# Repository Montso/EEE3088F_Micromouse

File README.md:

# EEE3080F Micromouse Project
This repo consists of the KiCAD files the sensing and power components of the micromouse project.

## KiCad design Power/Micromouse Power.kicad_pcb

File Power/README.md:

Power board for the micromouse projecct under EEE3088F.

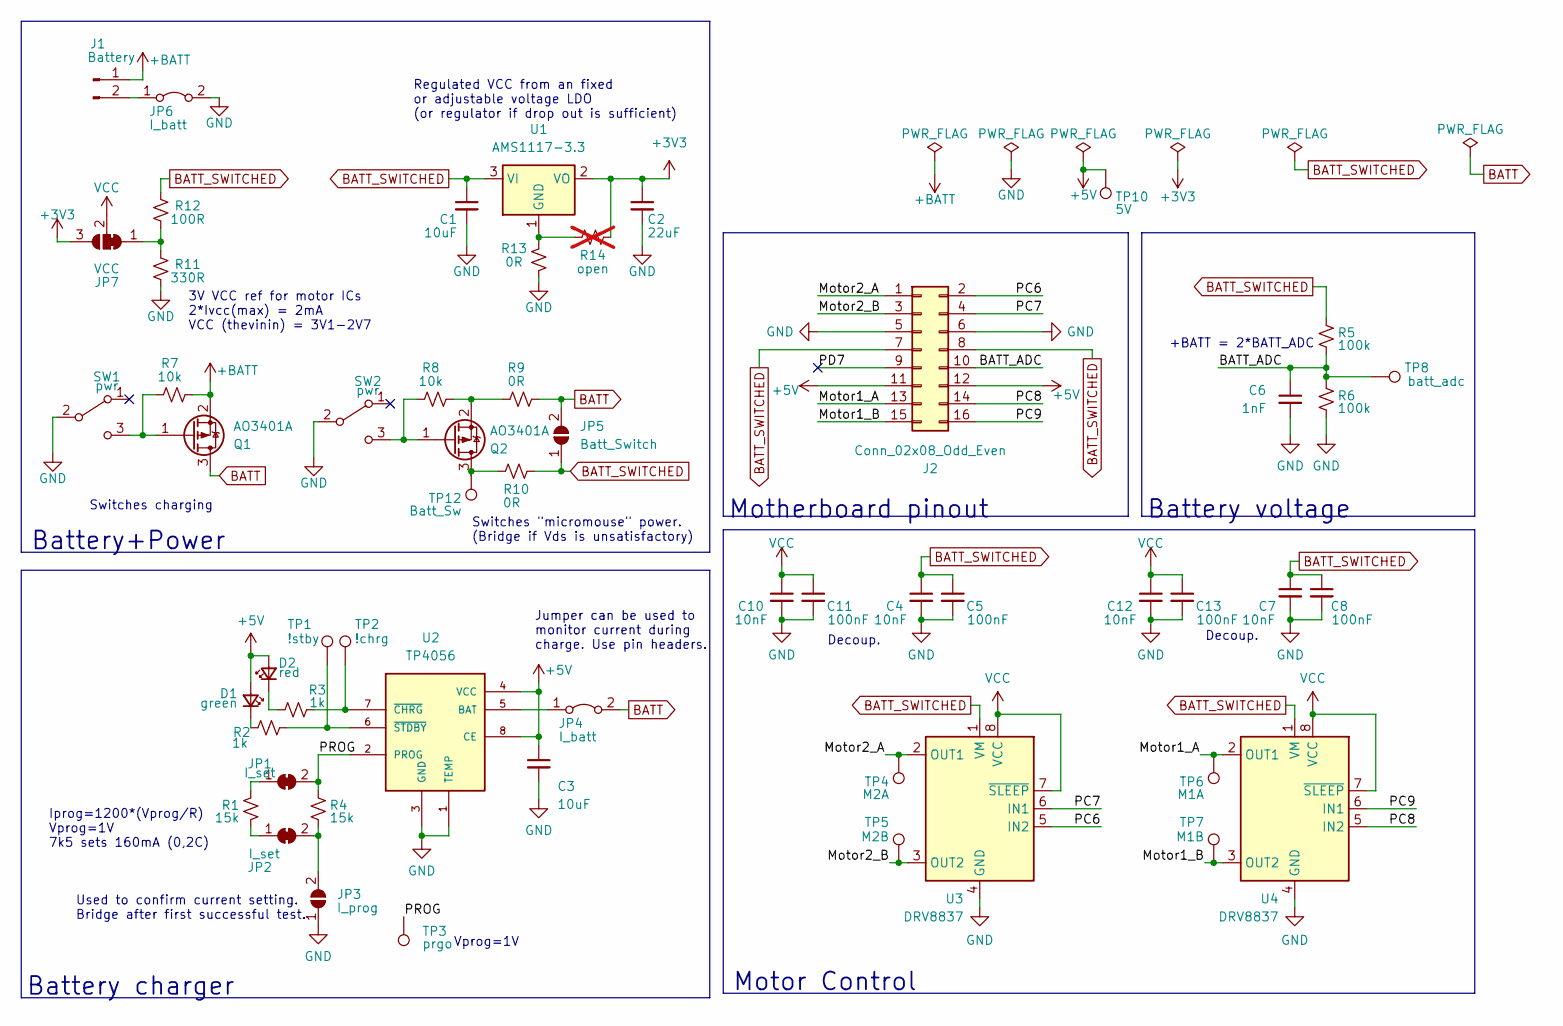
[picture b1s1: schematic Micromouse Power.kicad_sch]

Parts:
C1, C3: 10uF; C_0603_1608Metric; LCSC C19702
C2: 22uF; C_0603_1608Metric; LCSC C59461
C4, C7, C10, C12: 10nF; C_0603_1608Metric; LCSC C57112
C5, C8, C11, C13: 100nF; C_0603_1608Metric; LCSC C14663
C6: 1nF; C_0603_1608Metric; LCSC C1588
D1: green; LED_0603_1608Metric; LCSC C72038
D2: red; LED_0603_1608Metric; LCSC C2286
J1: Battery; JST_PH_S2B-PH-K_1x02_P2.00mm_Horizontal
J2: Conn_02x08_Odd_Even; PinHeader_2x08_P2.54mm_Vertical
JP1, JP2: I_set; SolderJumper-2_P1.3mm_Bridged_RoundedPad1.0x1.5mm
JP3: I_prog; SolderJumper-2_P1.3mm_Open_RoundedPad1.0x1.5mm
JP4, JP6: I_batt; PinHeader_1x02_P2.54mm_Vertical
JP5: Batt_Switch; SolderJumper-2_P1.3mm_Open_RoundedPad1.0x1.5mm
JP7: VCC; SolderJumper-3_P1.3mm_Bridged12_Pad1.0x1.5mm_NumberLabels
Q1, Q2: AO3401A; SOT-23; LCSC C15127
R1, R4: 15k; R_0805_2012Metric_Pad1.20x1.40mm_HandSolder; LCSC C17475
R2, R3: 1k; R_0603_1608Metric_Pad0.98x0.95mm_HandSolder; LCSC C21190
R5, R6: 100k; R_0603_1608Metric_Pad0.98x0.95mm_HandSolder; LCSC C25803
R7, R8: 10k; R_0603_1608Metric_Pad0.98x0.95mm_HandSolder; LCSC C25804
R9, R10, R13: 0R; R_0603_1608Metric_Pad0.98x0.95mm_HandSolder; LCSC C21189
R11: 330R; R_0603_1608Metric_Pad0.98x0.95mm_HandSolder; LCSC C23138
R12: 100R; R_0603_1608Metric_Pad0.98x0.95mm_HandSolder; LCSC C22775
R14: open; R_0603_1608Metric_Pad0.98x0.95mm_HandSolder; not fitted
SW1, SW2: pwr; SMD_SPDT; LCSC C145857
TP1: !stby; TestPoint_Pad_D1.0mm
TP2: !chrg; TestPoint_Pad_D1.0mm
TP3: prgo; TestPoint_Pad_D1.0mm
TP4: M2A; TestPoint_Pad_D1.0mm
TP5: M2B; TestPoint_Pad_D1.0mm
TP6: M1A; TestPoint_Pad_D1.0mm
TP7: M1B; TestPoint_Pad_D1.0mm
TP8: batt_adc; TestPoint_Pad_D1.0mm
TP10: 5V; TestPoint_Pad_D1.0mm
TP12: Batt_Sw; TestPoint_Pad_D1.0mm
U1: AMS1117-3.3; SOT-223-3_TabPin2; LCSC C6186
U2: TP4056; SOP127P600X175-9N; LCSC C16581
U3, U4: DRV8837; WSON-8-1EP_2x2mm_P0.5mm_EP0.9x1.6mm; LCSC C191000

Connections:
+3V3: C2.1, JP7.3 (B), R14.1, U1.2 (VO)
+5V: C3.1, D1.2 (A), D2.2 (A), J2.11, J2.12, TP10.1, U2.4 (VCC), U2.8 (CE)
+BATT: J1.1, Q1.2 (S), R7.1
/BATT_ADC: C6.1, J2.10, R5.1, R6.2, TP8.1
/Motor1_A: J2.13, TP6.1, U4.2 (OUT1)
/Motor1_B: J2.15, TP7.1, U4.3 (OUT2)
/Motor2_A: J2.1, TP4.1, U3.2 (OUT1)
/Motor2_B: J2.3, TP5.1, U3.3 (OUT2)
/PC6: J2.2, U3.5 (IN2)
/PC7: J2.4, U3.6 (IN1)
/PC8: J2.14, U4.5 (IN2)
/PC9: J2.16, U4.6 (IN1)
/PD7: J2.9
/PROG: JP1.2 (B), R4.2, TP3.1, U2.2 (PROG)
BATT: JP4.2 (B), JP5.2 (B), Q1.3 (D), R9.1
BATT_SWITCHED: C1.1, C4.1, C5.1, C7.1, C8.1, J2.7, J2.8, JP5.1 (A), R5.2, R10.2, R12.1, U1.3 (VI), U3.1 (VM), U4.1 (VM)
GND: C1.2, C2.2, C3.2, C4.2, C5.2, C6.2, C7.2, C8.2, C10.2, C11.2, C12.2, C13.2, J2.5, J2.6, JP3.1 (A), JP6.2 (B), R6.1, R11.2, R13.1, SW1.2 (B), SW2.2 (B), U2.1 (TEMP), U2.3 (GND), U3.4 (GND), U3.9 (GND), U4.4 (GND), U4.9 (GND)
unnamed: D1.1 (K), R2.1
unnamed: D2.1 (K), R3.1
unnamed: J1.2, JP6.1 (A)
unnamed: JP1.1 (A), R1.2
unnamed: JP2.1 (A), R1.1
unnamed: JP2.2 (B), JP3.2 (B), R4.1
unnamed: JP4.1 (A), U2.5 (BAT)
unnamed: JP7.1 (A), R11.1, R12.2
unnamed: Q1.1 (G), R7.2, SW1.3 (C)
unnamed: Q2.3 (D), R10.1, TP12.1
unnamed: Q2.1 (G), R8.2, SW2.3 (C)
unnamed: Q2.2 (S), R8.1, R9.2
unnamed: R13.2, R14.2, U1.1 (GND)
unnamed: R3.2, TP2.1, U2.7 (~CHRG)
unnamed: R2.2, TP1.1, U2.6 (~STDBY)
VCC: C10.1, C11.1, C12.1, C13.1, JP7.2 (C), U3.7 (~SLEEP), U3.8 (VCC), U4.7 (~SLEEP), U4.8 (VCC)

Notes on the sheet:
Battery+Power
Regulated VCC from an fixed or adjustable voltage LDO (or regulator if drop out is sufficient)
Vprog=1V
Motherboard pinout
+BATT = 2*BATT_ADC
Decoup.
Used to confirm current setting. Bridge after first successful test.
Motor Control
Switches "micromouse" power. (Bridge if Vds is unsatisfactory)
3V VCC ref for motor ICs 2*Ivcc(max) = 2mA VCC (thevinin) = 3V1-2V7
Switches charging
Battery voltage
Battery charger
Iprog=1200*(Vprog/R) Vprog=1V 7k5 sets 160mA (0,2C)
Jumper can be used to monitor current during charge. Use pin headers.

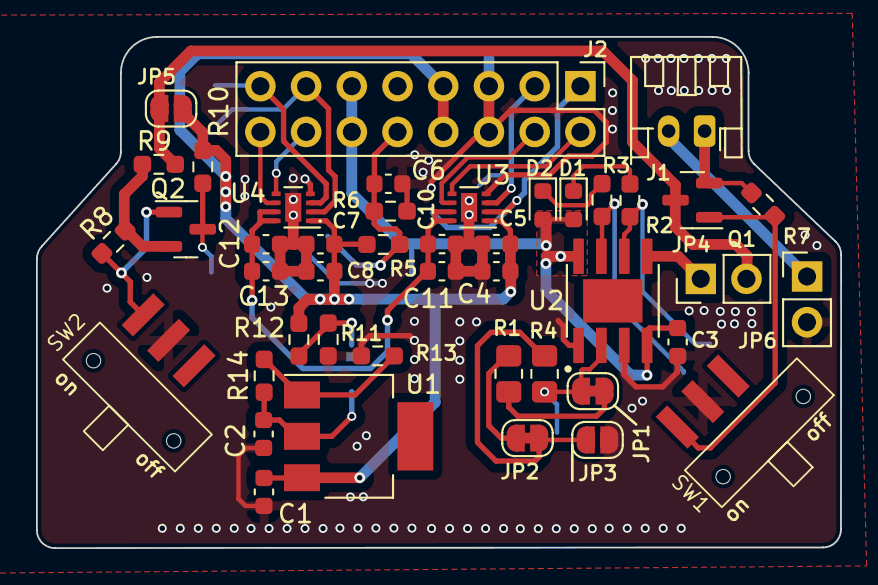
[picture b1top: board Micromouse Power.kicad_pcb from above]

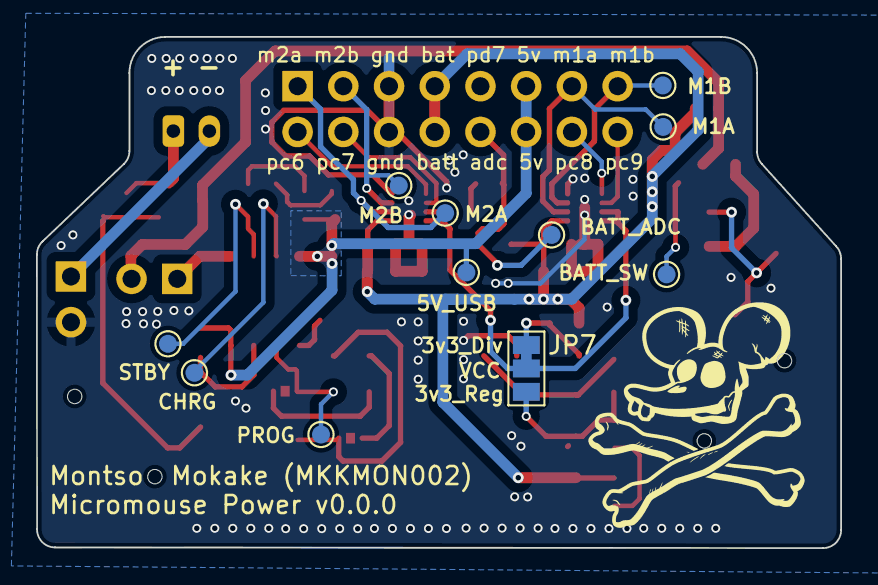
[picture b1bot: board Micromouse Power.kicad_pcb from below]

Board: 2 copper layers, 44.7 x 28.4 mm, 55 parts (11 on the bottom side), 32 nets.

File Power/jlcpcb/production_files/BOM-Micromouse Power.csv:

Comment,Designator,Footprint,LCSC
pwr,"SW1,SW2",SMD_SPDT,C145857
100nF,"C11,C13,C5,C8",C_0603_1608Metric,C14663
AO3401A,"Q1,Q2",SOT-23,C15127
1nF,C6,C_0603_1608Metric,C1588
TP4056,U2,SOP127P600X175-9N,C16581
15k,"R1,R4",R_0805_2012Metric_Pad1.20x1.40mm_HandSolder,C17475
DRV8837,"U3,U4",WSON-8-1EP_2x2mm_P0.5mm_EP0.9x1.6mm,C191000
10uF,"C1,C3",C_0603_1608Metric,C19702
0R,"R10,R13,R9",R_0603_1608Metric_Pad0.98x0.95mm_HandSolder,C21189
1k,"R2,R3",R_0603_1608Metric_Pad0.98x0.95mm_HandSolder,C21190
100R,R12,R_0603_1608Metric_Pad0.98x0.95mm_HandSolder,C22775
red,D2,LED_0603_1608Metric,C2286
330R,R11,R_0603_1608Metric_Pad0.98x0.95mm_HandSolder,C23138
100k,"R5,R6",R_0603_1608Metric_Pad0.98x0.95mm_HandSolder,C25803
10k,"R7,R8",R_0603_1608Metric_Pad0.98x0.95mm_HandSolder,C25804
10nF,"C10,C12,C4,C7",C_0603_1608Metric,C57112
22uF,C2,C_0603_1608Metric,C59461
AMS1117-3.3,U1,SOT-223-3_TabPin2,C6186
green,D1,LED_0603_1608Metric,C72038

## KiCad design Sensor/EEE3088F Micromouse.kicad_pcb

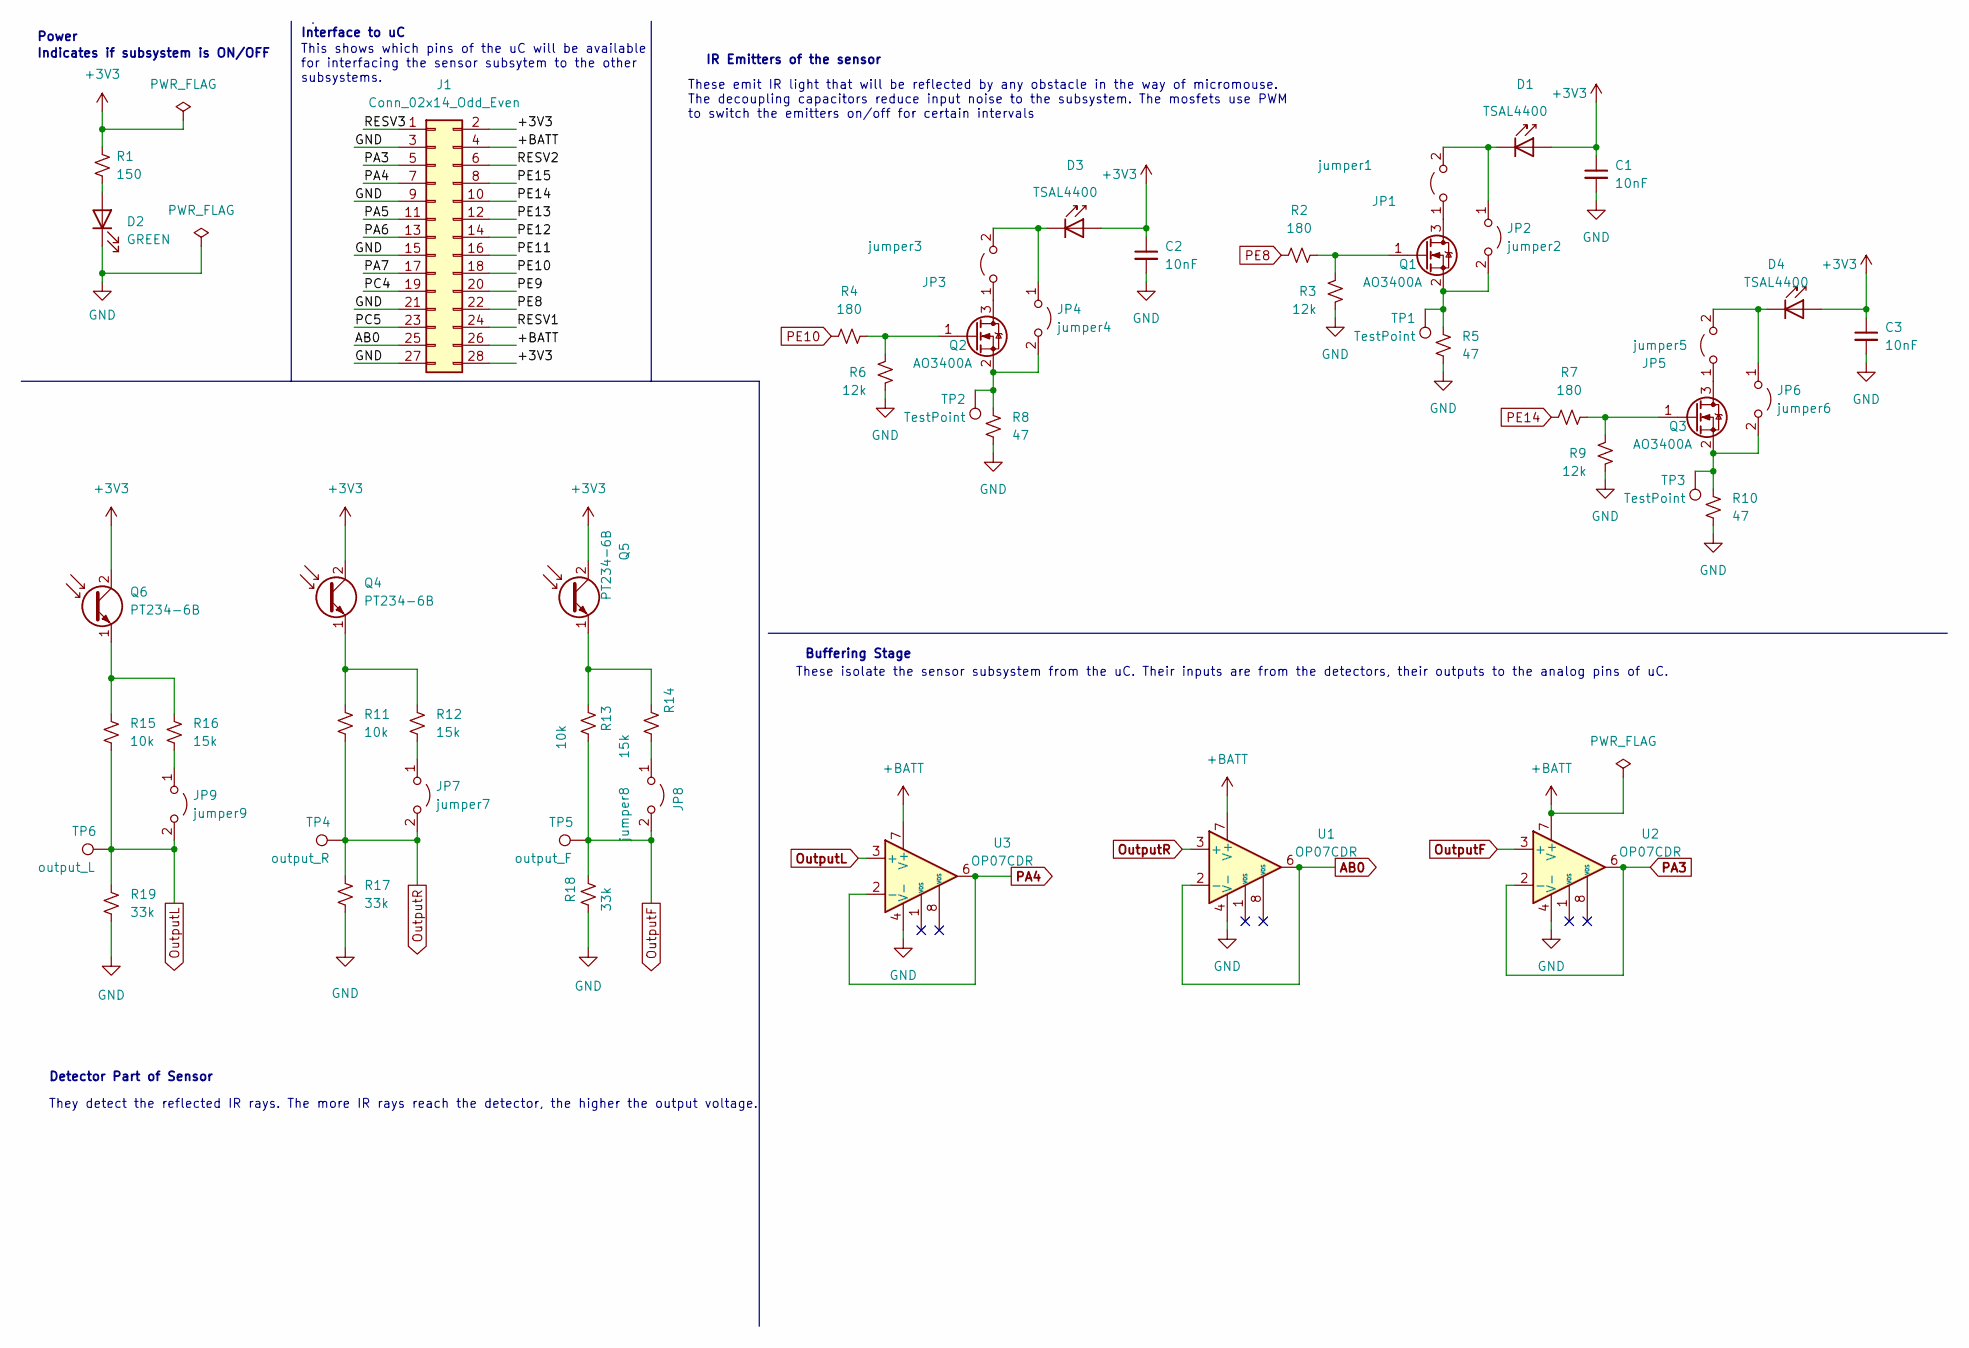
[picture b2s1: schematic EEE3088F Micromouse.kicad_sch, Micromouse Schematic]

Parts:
C1, C2, C3: 10nF; C_0805_2012Metric
D1, D3, D4: TSAL4400; LED_D3.0mm_Horizontal_O1.27mm_Z2.0mm
D2: GREEN; LED_0805_2012Metric
J1: Conn_02x14_Odd_Even; PinHeader_2x14_P2.54mm_Vertical
JP1: jumper1; SolderJumper-2_P1.3mm_Open_Pad1.0x1.5mm
JP2: jumper2; SolderJumper-2_P1.3mm_Open_Pad1.0x1.5mm
JP3: jumper3; SolderJumper-2_P1.3mm_Open_Pad1.0x1.5mm
JP4: jumper4; SolderJumper-2_P1.3mm_Open_Pad1.0x1.5mm
JP5: jumper5; SolderJumper-2_P1.3mm_Open_Pad1.0x1.5mm
JP6: jumper6; SolderJumper-2_P1.3mm_Open_Pad1.0x1.5mm
JP7: jumper7; SolderJumper-2_P1.3mm_Open_Pad1.0x1.5mm
JP8: jumper8; SolderJumper-2_P1.3mm_Open_Pad1.0x1.5mm
JP9: jumper9; SolderJumper-2_P1.3mm_Open_Pad1.0x1.5mm
Q1, Q2, Q3: AO3400A; SOT-23
Q4, Q5, Q6: PT234-6B
R1: 150; R_0805_2012Metric
R2, R4, R7: 180; R_0805_2012Metric
R3, R6, R9: 12k; R_0805_2012Metric
R5, R8, R10: 47; R_0805_2012Metric
R11, R13, R15: 10k; R_0805_2012Metric
R12, R14, R16: 15k; R_0805_2012Metric
R17, R18, R19: 33k; R_0805_2012Metric
TP1, TP2, TP3: TestPoint; TestPoint_Pad_D3.0mm
TP4: output_R; TestPoint_Pad_D3.0mm
TP5: output_F; TestPoint_Pad_D3.0mm
TP6: output_L; TestPoint_Pad_D3.0mm
U1, U2, U3: OP07CDR; SOIC127P599X175-8N

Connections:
+3V3: C1.1, C2.1, C3.1, D1.2 (A), D3.2 (A), D4.2 (A), J1.2, J1.28, Q4.2 (C), Q5.2 (C), Q6.2 (C), R1.1
+BATT: J1.4, J1.26, U1.7 (V+), U2.7 (V+), U3.7 (V+)
/PA5: J1.11
/PA6: J1.13
/PA7: J1.17
/PC4: J1.19
/PC5: J1.23
/PE9: J1.20
/PE11: J1.16
/PE12: J1.14
/PE13: J1.12
/PE15: J1.8
/RESV1: J1.24
/RESV2: J1.6
/RESV3: J1.1
AB0: J1.25, U1.2 (-), U1.6
GND: C1.2, C2.2, C3.2, D2.1 (K), J1.3, J1.9, J1.15, J1.21, J1.27, R3.2, R5.2, R6.2, R8.2, R9.2, R10.2, R17.2, R18.2, R19.2, U1.4 (V-), U2.4 (V-), U3.4 (V-)
unnamed: D1.1 (K), JP1.2 (B), JP2.1 (A)
unnamed: D2.2 (A), R1.2
unnamed: D3.1 (K), JP3.2 (B), JP4.1 (A)
unnamed: D4.1 (K), JP5.2 (B), JP6.1 (A)
unnamed: JP1.1 (A), Q1.3 (D)
unnamed: JP2.2 (B), Q1.2 (S), R5.1, TP1.1
unnamed: JP3.1 (A), Q2.3 (D)
unnamed: JP4.2 (B), Q2.2 (S), R8.1, TP2.1
unnamed: JP5.1 (A), Q3.3 (D)
unnamed: JP6.2 (B), Q3.2 (S), R10.1, TP3.1
unnamed: JP7.1 (A), R12.2
unnamed: JP8.1 (A), R14.2
unnamed: JP9.1 (A), R16.2
unnamed: Q1.1 (G), R2.2, R3.1
unnamed: Q2.1 (G), R4.2, R6.1
unnamed: Q3.1 (G), R7.2, R9.1
unnamed: Q4.1 (E), R11.1, R12.1
unnamed: Q5.1 (E), R13.1, R14.1
unnamed: Q6.1 (E), R15.1, R16.1
OutputF: JP8.2 (B), R13.2, R18.1, TP5.1, U2.3 (+)
OutputL: JP9.2 (B), R15.2, R19.1, TP6.1, U3.3 (+)
OutputR: JP7.2 (B), R11.2, R17.1, TP4.1, U1.3 (+)
PA3: J1.5, U2.2 (-), U2.6
PA4: J1.7, U3.2 (-), U3.6
PE8: J1.22, R2.1
PE10: J1.18, R4.1
PE14: J1.10, R7.1

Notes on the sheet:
IR Emitters of the sensor
These emit IR light that will be reflected by any obstacle in the way of micromouse. The decoupling capacitors reduce input noise to the subsystem. The mosfets use PWM to switch the emitters on/off for certain intervals
This shows which pins of the uC will be available for interfacing the sensor subsytem to the other subsystems.
They detect the reflected IR rays. The more IR rays reach the detector, the higher the output voltage.
Interface to uC
Indicates if subsystem is ON/OFF
Detector Part of Sensor
These isolate the sensor subsystem from the uC. Their inputs are from the detectors, their outputs to the analog pins of uC.
Buffering Stage
Power

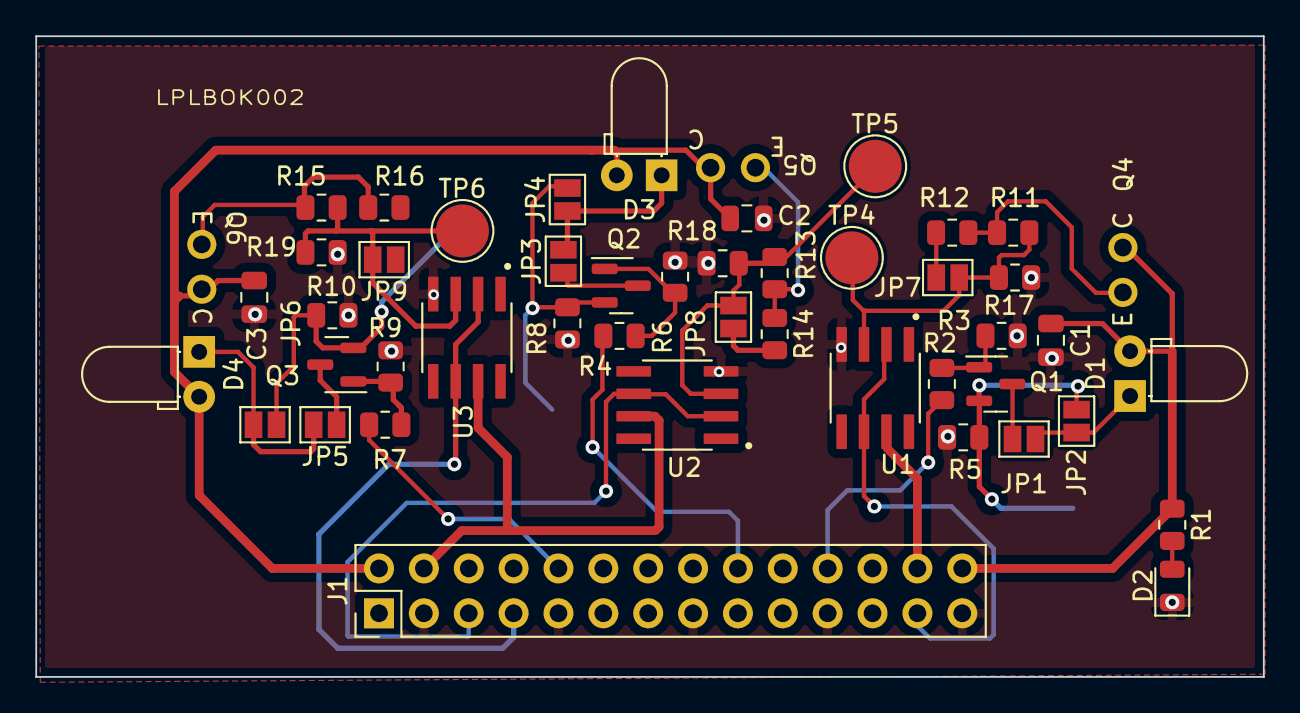
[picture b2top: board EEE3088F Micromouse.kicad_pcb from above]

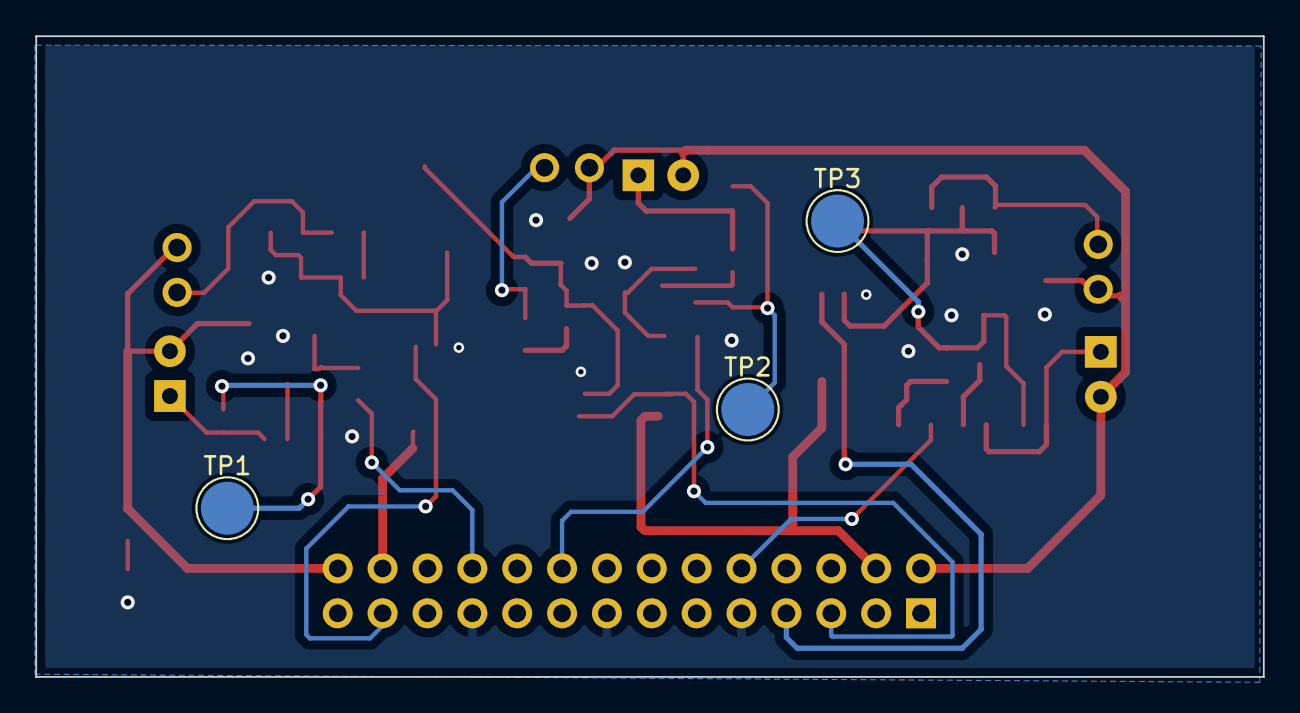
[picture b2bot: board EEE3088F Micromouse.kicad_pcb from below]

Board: 2 copper layers, 69.5 x 36.3 mm, 51 parts (3 on the bottom side), 31 nets.

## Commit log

2024-03-14 Added additional libraries
2024-03-14 Created power sub-dir
2024-03-14 Created Sensor sub-dir
2024-03-14 Created motor, charger, and sens schematics
2024-03-15 Added power flags
2024-03-15 Added test points and i_prog jumper.
2024-03-16 Added more test points and jumpers.
2024-03-16 Updated GPIO PC6-9 label on 08 connector
2024-03-16 Assigned some footprints
2024-03-17 Updated .gitignore
2024-03-17 Added IC lcsc numbers
2024-03-17 Delete Sensor/Micromouse Sensing.kicad_pcb
    Not appropriate version for me
2024-03-17 Delete Sensor/Micromouse Sensing.kicad_pro
    version problem
2024-03-17 Delete Sensor/Micromouse Sensing.kicad_sch
    version problem
2024-03-17 Added switched +batt
2024-03-18 Added drv8837 libraries
2024-03-18 Changed motor IC to drv8837
2024-03-18 Added 3v3 LDO
2024-03-18 Assigned footprints. Except switch
2024-03-18 Populated pcb
2024-03-18 Updated document details
2024-03-19 Imported pcb design rules
2024-03-19 Added Hor. battery connector. Temp switch ft.
2024-03-19 Added 3v3 decoup for drv8837
2024-03-20 PCB routing optimisation
2024-03-20 Initial board layout done
2024-03-20 Added pmos+switch circuit
2024-03-20 Added switch circuit
2024-03-21 Assigned footprints, hor. jst and switches
2024-03-21 Removed power decoup
2024-03-21 Routing and removes power decoup
2024-03-21 Updated routing
2024-03-21 Updated schematic
2024-03-21 Updated project mappings
2024-03-22 Updated document titles
2024-03-22 Fixed charge-power switching
2024-03-22 Added switch silkscreen
2024-03-22 Fixed M2 testpoints
2024-03-22 Review and touchups
    -added silkscreen art and info
    -fixed tp4056 decoupling
2024-03-22 Final review and title info
2024-03-23 Added datasheets and jlcpcb files
2024-03-23 Updated project file
2024-03-23 Added voltage divider for VCC
2024-03-23 Added VCC divider for driver.
    -Jumper to select VCC
    -Stitching vias
    -Silkscreen
2024-03-23 Fixed tab width
2024-03-23 Added jlcpcb files
2024-03-24 Add files via upload
    PROJECT FILES AS AT 24/03/2024
2024-04-05 Delete Sensor/datasheets/1811101704_Vishay-Intertech-TSAL6100_C111836.pdf
    Part not on JLCPCB
2024-04-05 Delete Sensor/datasheets/asset_pdf_5174731.pdf
    Replace with phototransistor.
2024-04-05 Delete Sensor/datasheets/2206171645_OSRAM-Opto-Semicon-SFH-2400-FA-Z_C2900223.pdf
    Prefer through-holes for this part.
2024-04-05 Delete Sensor/datasheets/1809042023_ST-Semtech-2N3904_C118538.pdf
    Replace with op-amp.
2024-04-05 Add files via upload
    OP07CDR op-amp for buffer.
2024-04-05 Add files via upload
    Mosfet for switching the IR-emitter on/off
2024-04-05 Add files via upload
    Phototransistor for detection.
2024-04-05 Delete Sensor/EEE3088F Micromouse.kicad_pcb
    Older schematic
2024-04-05 Delete Sensor/EEE3088F Micromouse.kicad_pro
    Older project file
2024-04-05 Delete Sensor/EEE3088F Micromouse.kicad_sch
    Older schematic
2024-04-05 Add files via upload
    Updated kicad project files
2024-04-05 Add files via upload
    Additional footprints used.
2024-04-05 Add files via upload
    STM32L476 files
2024-04-05 Added student card to silkscreen
2024-04-07 Added comments for battery schematics
2024-04-07 Updated jlcpcb files
2024-04-08 Fixed conflict schematic
2024-04-08 Fixed pcb file
2024-04-08 Fixed project file
2024-04-09 Updated schematic notes
2024-04-18 Updated text on schematic
